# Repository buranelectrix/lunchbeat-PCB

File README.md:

lunchbeat - 1bit groovebox - PCB version
========================================
by Jan Cumpelik (jan@buranelectrix.com)

Hi. Here it is, Lunchbeat made it from breadboard to printed circuit board :)

"lunchbeat-PCB-firmware" contains source C code for Atmega328p 

"lunchbeat-PCB-hardware" contains resources for building Lunchbeat. Schematics, printed circuit board design. And whole Kicad project including library with used parts :)  Kicad is nice free software, use it :)

Feel free to use these files (read license first).

If you use this to create something cool, please let me know! 
If you find any flaw, please let me know!

Thank you, Jan.

The firmware is released under a GPL3.0 license.
The PCB layout and schematics are released under cc-by-sa 3.0 license. 

more info: www.buranelectrix.com

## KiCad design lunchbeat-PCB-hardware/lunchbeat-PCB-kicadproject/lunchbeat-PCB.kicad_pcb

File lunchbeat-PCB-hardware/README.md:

Lunchbeat hardware
==================

here you can find:

- whole KiCad project with latest Lunchbeat hardware revision

- partlist

- schematics

Part list now included in ODS file (OpenDocument Spreadsheet).

Jan

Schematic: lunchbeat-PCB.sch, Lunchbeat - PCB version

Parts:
6PIN1: ISP6PIN
B1: BATTERY
BUTT1: HIHAT
BUTT2: KICK
BUTT3: PLAY/STOP
BUTT4: RESET
BUTT5: SNARE
BUTT6: BASS
BUTT7: STEPEDIT
C1, C2: 22p
C3: 10u
C4: 330n
C5, C7, C8, C9: 100n
C6: 220u
D1, D2, D3, D4, D5, D6, D7, D8, D9, D10: LED
J1: AUDIO OUT
J2: SYNC IN
R1, R2, R3, R4, R5, R6, R7, R8: 100k
R9, R10, R13, R14, R15, R16, R17: 10k
R11: 100R
R12, R18, R19, R20, R21, R22, R23, R24, R25, R26: R
SW1: SW-PW
U1: LM358N
U2: ATMEGA328P
U3: 74595
U4: 7805
XTAL1: 16MHZ

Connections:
/BASS: BUTT6.2, U2.5 (PD3)
/BASSPOT: R16.2, U2.24 (PC1)
/CLOCK: 6PIN1.3 (SCK), U2.19 (SCK/PB5), U3.11 (SRCLK)
/DAC BIT1: R3.2, U2.11 (PD5)
/DAC BIT2: R2.2, U2.12 (PD6)
/DAC BIT3: R1.2, U2.13 (PD7)
/DAC out: R1.1, R4.2, R6.2, U1.3 (+)
/DATA: 6PIN1.4 (MOSI), U2.17 (MOSI/PB3), U3.14 (SER)
/EDIT: BUTT7.2, U2.14 (PB0)
/HIHAT: BUTT1.2, U2.2 (PD0)
/HIHATPOT: R15.2, U2.25 (PC2)
/KICK: BUTT2.2, U2.4 (PD2)
/KICKPOT: R13.2, U2.27 (SDA/PC4)
/LATCH: U2.16 (PB2), U3.12 (RCLK)
/MISO: 6PIN1.1 (MISO), U2.18 (MISO/PB4)
/PLAY: BUTT3.2, U2.6 (PD4)
/RESET: 6PIN1.5 (RESET), BUTT4.2, R10.1, U2.1 (RESET)
/SNARE: BUTT5.2, U2.3 (PD1)
/SNAREPOT: R14.2, U2.26 (PC3)
/TEMPOPOT: R17.2, U2.23 (PC0)
/batvcc: B1.2 (+), SW1.1
unnamed: D10.1, R26.1
unnamed: R9.3, U1.1, U1.2 (-)
unnamed: R9.2, R11.1
unnamed: C3.1, R11.2
unnamed: C4.2, SW1.2, U4.1 (IN)
unnamed: D1.2, R12.2
unnamed: D1.1, U2.15 (PB1)
unnamed: C2.2, U2.10 (PB7/X2), XTAL1.1
unnamed: J2.1, U2.28 (SCL/PC5)
unnamed: R2.1, R4.1, R5.2, R6.1, R7.2
unnamed: C1.2, U2.9 (PB6/X1), XTAL1.2
unnamed: C3.2, J1.1
unnamed: D6.1, R22.2
unnamed: D5.1, R21.2
unnamed: D4.1, R20.2
unnamed: D3.1, R19.2
unnamed: D2.1, R18.2
unnamed: R18.1, U3.7 (QH)
unnamed: R19.1, U3.6 (QG)
unnamed: R20.1, U3.5 (QF)
unnamed: R21.1, U3.4 (QE)
unnamed: R22.1, U3.3 (QD)
unnamed: R25.1, U3.15 (QA)
unnamed: D9.1, R25.2
unnamed: R24.1, U3.1 (QB)
unnamed: D8.1, R24.2
unnamed: R23.1, U3.2 (QC)
unnamed: D7.1, R23.2
unnamed: R3.1, R5.1, R7.1, R8.1
VCC: 6PIN1.2 (VCC), C5.2, C6.1, C7.2, C8.2, C9.2, R10.2, R13.3, R14.3, R15.3, R16.3, R17.3, R26.2, U1.8 (V+), U2.7 (VCC), U2.20 (AVCC), U2.21 (AREF), U3.10 (/SRCLR), U3.16 (VCC), U4.3 (OUT)
~: 6PIN1.6 (GND), B1.1 (-), BUTT1.1, BUTT2.1, BUTT3.1, BUTT4.1, BUTT5.1, BUTT6.1, BUTT7.1, C1.1, C2.1, C4.1, C5.1, C6.2, C7.1, C8.1, C9.1, D2.2, D3.2, D4.2, D5.2, D6.2, D7.2, D8.2, D9.2, D10.2, J1.3, J2.3, R8.2, R9.1, R12.1, R13.1, R14.1, R15.1, R16.1, R17.1, U1.4 (V-), U2.8 (GND), U2.22 (GND), U3.8 (GND), U3.13 (/OE), U4.2 (GND)

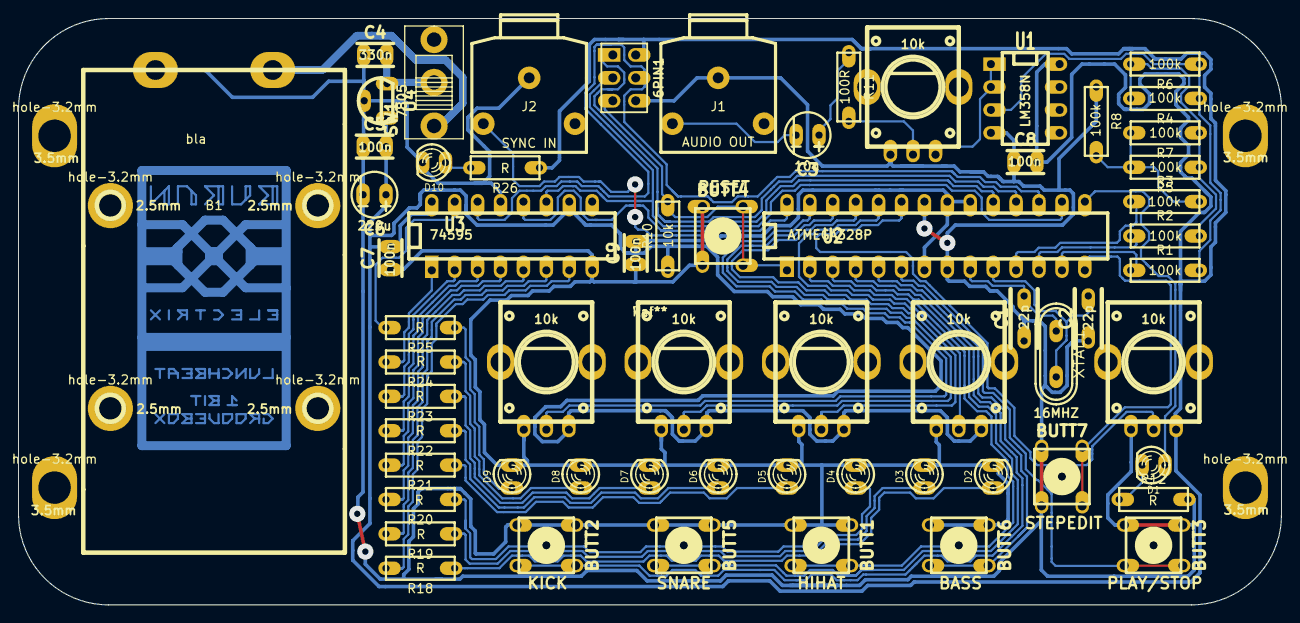
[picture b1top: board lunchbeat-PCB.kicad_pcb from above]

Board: 2 copper layers, 140.0 x 65.0 mm, 72 parts (0 on the bottom side), 52 nets.

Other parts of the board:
Ref**: bla; buran-lunch-17x32-med
Ref**#2: Val**; lunchdeska1-l20
hole-3.2mm, hole-3.2mm#2, hole-3.2mm#3, hole-3.2mm#4: 2.5mm; hole-oval-3.2mm
hole-3.2mm#5, hole-3.2mm#6, hole-3.2mm#7, hole-3.2mm#8: 3.5mm; hole-oval-3.2mm

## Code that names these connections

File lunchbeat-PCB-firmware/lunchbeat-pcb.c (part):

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
#define NOW 	0
#define PREV 	1
#define PLAY 	4
#define EDIT 	5
uint8_t rawbutton = 0; 
uint8_t button[2][6] = {{0,0,0,0,0,0},{0,0,0,0,0,0}} ; 	
uint8_t seq[8] = {	0b00000001,
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uint8_t ledbarhlf = 0;
uint16_t pot[5];

#define KICKPOT		4
#define SNAREPOT	3
#define HATPOT		2
#define WAVEPOT		1
#define TEMPOPOT	0

#define KICK 	0
#define SNARE 	1
#define HAT 	2
#define WAVE	3
#define TEMPO	4
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uint8_t division = 1;
uint8_t subdiv = 1;

#define TEMPOLED_OFF PORTB &= ~(1 << PB1)
#define TEMPOLED_ON  PORTB |= (1 << PB1)
		

/////////////////////////////////////////////////
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		uint8_t rawbutton = ~(PIND) & 0b00011111;

		// exchange kick and hat buttons - hardware issue
		if (~(PIND) & (1<<KICK)) {rawbutton |= (1<<HAT);} else {rawbutton &= ~(1<<HAT);}
		if (~(PIND) & (1<<HAT)) {rawbutton |= (1<<KICK);} else {rawbutton &= ~(1<<KICK);}

		if (~(PINB) & (1<<PB0)) rawbutton |= 0b00100000; // pridame edit tlacitko z portu B
								 // add EDIT button from B port

		// debouncing
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				if (setmode) {
					if (extsyncmode) {
						extsyncmode = 0;
					//	DDRC |= (1 << PC5);
						PORTC &= ~(1 << PC5);
					}
					else {
						extsyncmode = 1;
					//	DDRC &= ~(1 << PC5);
						PORTC &= ~(1 << PC5);
					}
				}
				else if (playing) {
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						playstep = 0;
						newstep = 1;
						subdiv = division;
						PORTC |= (1 << PC5);
						tempo = 5500 - (pot[TEMPOPOT] << 2);
					}	
					playing = 1;
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		if (extsyncmode) { // externi clock
	
			// zmena na trig in na MISO pinu
			//if (PINC & (1 << PC5)) {trigpin = 1;} else {trigpin = 0;}
			if (PINB & (1 << PB4)) {trigpin = 1;} else {trigpin = 0;}

			// novy krok 
			// new step
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					newstep = 1;
					playstep ++;
					if (playstep > 7) playstep = 0;
					PORTC |= (1 << PC5); //trigout on
				}
			}
			
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				subdiv --;
				if (subdiv == 0) {
					subdiv = division ;
					PORTC |= (1 << PC5); // trigout on
				}
			}
		}
		
		// trig out off
		if (counter > 0x8f) {  // cca 10ms
			PORTC &= ~(1 << PC5);
		}

	}
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	// sound modelling :)

	// kick
	static uint8_t kick = 0;
	static uint16_t kickfreq = 2;
	if (gate[KICK]) {
		if (gate[KICK] == 1) { // zvuk zrovna zacal - sound starts
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		}
		gate[KICK] ++;
		if (gate[KICK] > ((pot[KICKPOT] << 3) + 0x01ff)) { // cas pro konec zvuku - sound ends
			gate[KICK] = 0;  // ticho
			kick = 0;
		} 
		else { // zvuk hraje - sound plays
			if (gate[KICK] == kickfreq) {
				if (kick) {
					kick = 0;
				} else {
					kick = 1;
				}
				kickfreq += (kickfreq>>4) + (64-(pot[KICKPOT]>>4));
			}
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	}

	//snare 
	static uint8_t snare = 0;
	static uint16_t snarefreq = 2;
	static uint16_t snarelfsr = 0b0011010010100100; // seed pro linear feedback shift register
	if (gate[SNARE]) {
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		}
		gate[SNARE] ++;
		if (gate[SNARE] > ((pot[SNAREPOT]<<2) + 0x01ff)) { // cas pro konec zvuku - end of sound
			gate[SNARE] = 0;  // ticho - silence
			snare = 0;
		} else { 			// zvuk hraje - sound is playing
		// prvni cast zvuku - first part of sound
			if (gate[SNARE] < (pot[SNAREPOT] + 0x0090)) {
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	// prevodnik je na 5, 6 a 7 pinu portu D
	//
	// output to DAC
	// DAC is on PD5, PD6 and PD7 pins
	uint8_t portmp = (mix << 5);
	portmp |= 0b00011111;	// pullups on PD0 - PD4
	PORTD = portmp;


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		setled ++;
		if (setled > 500) {
			setled = 0;
			if (PORTB & (1 << PB1)) {
				TEMPOLED_OFF;
			} 
			else {
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	else {
		if (playing) {
			if (extsyncmode) {
				if (PINB & (1 << PB4)) {
					TEMPOLED_ON;
				} 
				else {
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		}
		else {
			if (extsyncmode) {
				if (PINC & (1 << PC5)) {
					if (darkcycle) {
						TEMPOLED_OFF;
					}
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	//
	static uint16_t setupcounter = 0;
	
	if (PINB & (1 << PB0)) {
		setupcounter = 0;
	} 
	else {
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
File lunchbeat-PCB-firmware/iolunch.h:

/*
 * =============================
 *   B U R A N E L E C T R I X 
 * =============================
 *
 *       L U N C H B E A T
 *
 *        1-bit groovebox 
 *
 * =============================
 *           iolunch.h
 *       for Lunchbeat 1.3
 * setup routine
 * ADC (reading pot) routines
 * SPI out (for LEDs) routine
 * =============================
 *     (c) 2013 Jan Cumpelik
 * =============================
 *
 */


void setup_lunchbeat() {
	
	// tlacitko EDIT - EDIT button
	DDRB &= ~(1 << PB0); // input
	PORTB |= (1 << PB0); // pullup on

	// tempo LED
	DDRB |= (1 << PB1);
	PORTB &= ~(1 << PB1);

	// port D - D0-D4 vstup, D5-D7 vystup
	// port D - D0-D4 input, D5-D7 output
	DDRD  = 0b11100000;
	PORTD = 0b00011111; 
	
	// trigout
	DDRC |= (1 << PC5);
	PORTC &= ~(1 << PC5);


	// interni ADC nastaveni
	// internal ADC setup
	//ADCSRA |= (0 << ADPS2) | (0 << ADPS1) | (0 << ADPS0); //   5   us
	//ADCSRA |= (0 << ADPS2) | (1 << ADPS1) | (0 << ADPS0); //   6.5 us
	ADCSRA |= (0 << ADPS2) | (1 << ADPS1) | (1 << ADPS0); //  10   us
	//ADCSRA |= (1 << ADPS2) | (0 << ADPS1) | (0 << ADPS0); //  17   us
	//ADCSRA |= (1 << ADPS2) | (0 << ADPS1) | (1 << ADPS0); //  29.6 us
	//ADCSRA |= (1 << ADPS2) | (1 << ADPS1) | (0 << ADPS0); //  56   us
	//ADCSRA |= (1 << ADPS2) | (1 << ADPS1) | (1 << ADPS0); // 112   us
	ADMUX |= (1 << REFS0);
	//ADMUX |= (1 << ADLAR); // left adjust - pro 8-bit cteni pouze ADCH
	//ADMUX &= ~(1 << ADLAR);
	ADCSRA |= (1 << ADEN); // enable ADC

	//SPI pins
	DDRB |= (1 << PB3); // mosi - vystup - output
	DDRB &= ~(1 << PB4); // miso - vstup - input
	DDRB |= (1 << PB5); // sck - vystup  - output

	DDRB |= (1 << PB2); // led latch pin
	PORTB &= ~(1 << PB2); // set low
	
	// SPI nastaveni
	SPCR &= ~(1<<SPR0) & ~(1<<SPR1); // rychlost - speed
	SPCR &= ~(1<<SPI2X);             // rychlost - speed
	SPCR |= (1<<DORD);               // data order
	SPCR |=  (1<<SPE) | (1<<MSTR);	// spi enable, spi master
	
	// interrupt nastaveni
	cli();
	//TCCR1A  = (1 << COM1A0);		// toggle OC1A pin (PB1) on compare match
	TCCR1B  = (1 << WGM12); 		// CTC mode
	TCCR1B |= (1 << CS11);			// prescaler 8
	TIMSK1 |= (1 << OCIE1A);		// ctc interrupt enable
	OCR1A = 128;						// 15625Hz

	sei();
}

void ledbarout(uint8_t value) {

	SPDR = value;
	while(!(SPSR & (1<<SPIF)));
	PORTB |= (1 << PB2); // latch it
	PORTB &= ~(1 << PB2);
}
	
uint8_t readpot8b(uint8_t p) 
{
	// set multiplexer
	p &= 7;
	ADMUX &= ~(7);
	ADMUX |= p;
	ADMUX |= (1<<ADLAR); // left adjust 
	// start ADC conversion
	ADCSRA |= (1 << ADSC); // start single conversion
	while (ADCSRA & (1 << ADSC)) {} // wait for result
	// use left adjusted ADCH
	uint8_t pot = ADCH;
	return pot;
}

uint16_t readpot10b(uint8_t p) 
{
	// set multiplexer
	p &= 7;
	ADMUX &= ~(7);
	ADMUX |= p;
	ADMUX &= ~(1<<ADLAR); // no left adjust 
	// start ADC conversion
	ADCSRA |= (1 << ADSC); // start single conversion
	while (ADCSRA & (1 << ADSC)) {} // wait for result
	// convert to 16 bit variable
	uint8_t potL = ADCL;
	uint8_t potH = ADCH;
	uint16_t pot = potH;
	pot <<= 8;
	pot |= potL;
	return pot;
}

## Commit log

2013-10-28 original upload
2013-11-06 revB
2013-11-07 version 1.2
2013-11-12 part list release
2013-12-27 kit1
2014-01-14 trig out in division fix

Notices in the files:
lunchbeat-PCB-hardware/lunchbeat-PCB-kicadproject/lunchbeat-PCB.kicad_pcb:
this PCB design is licensed under CC BY-SA3.0 license
lunchbeat-PCB-hardware/lunchbeat-PCB-kicadproject/lunchbeat-PCB.sch:
this schematics is released under a CC BY-SA3.0 license
